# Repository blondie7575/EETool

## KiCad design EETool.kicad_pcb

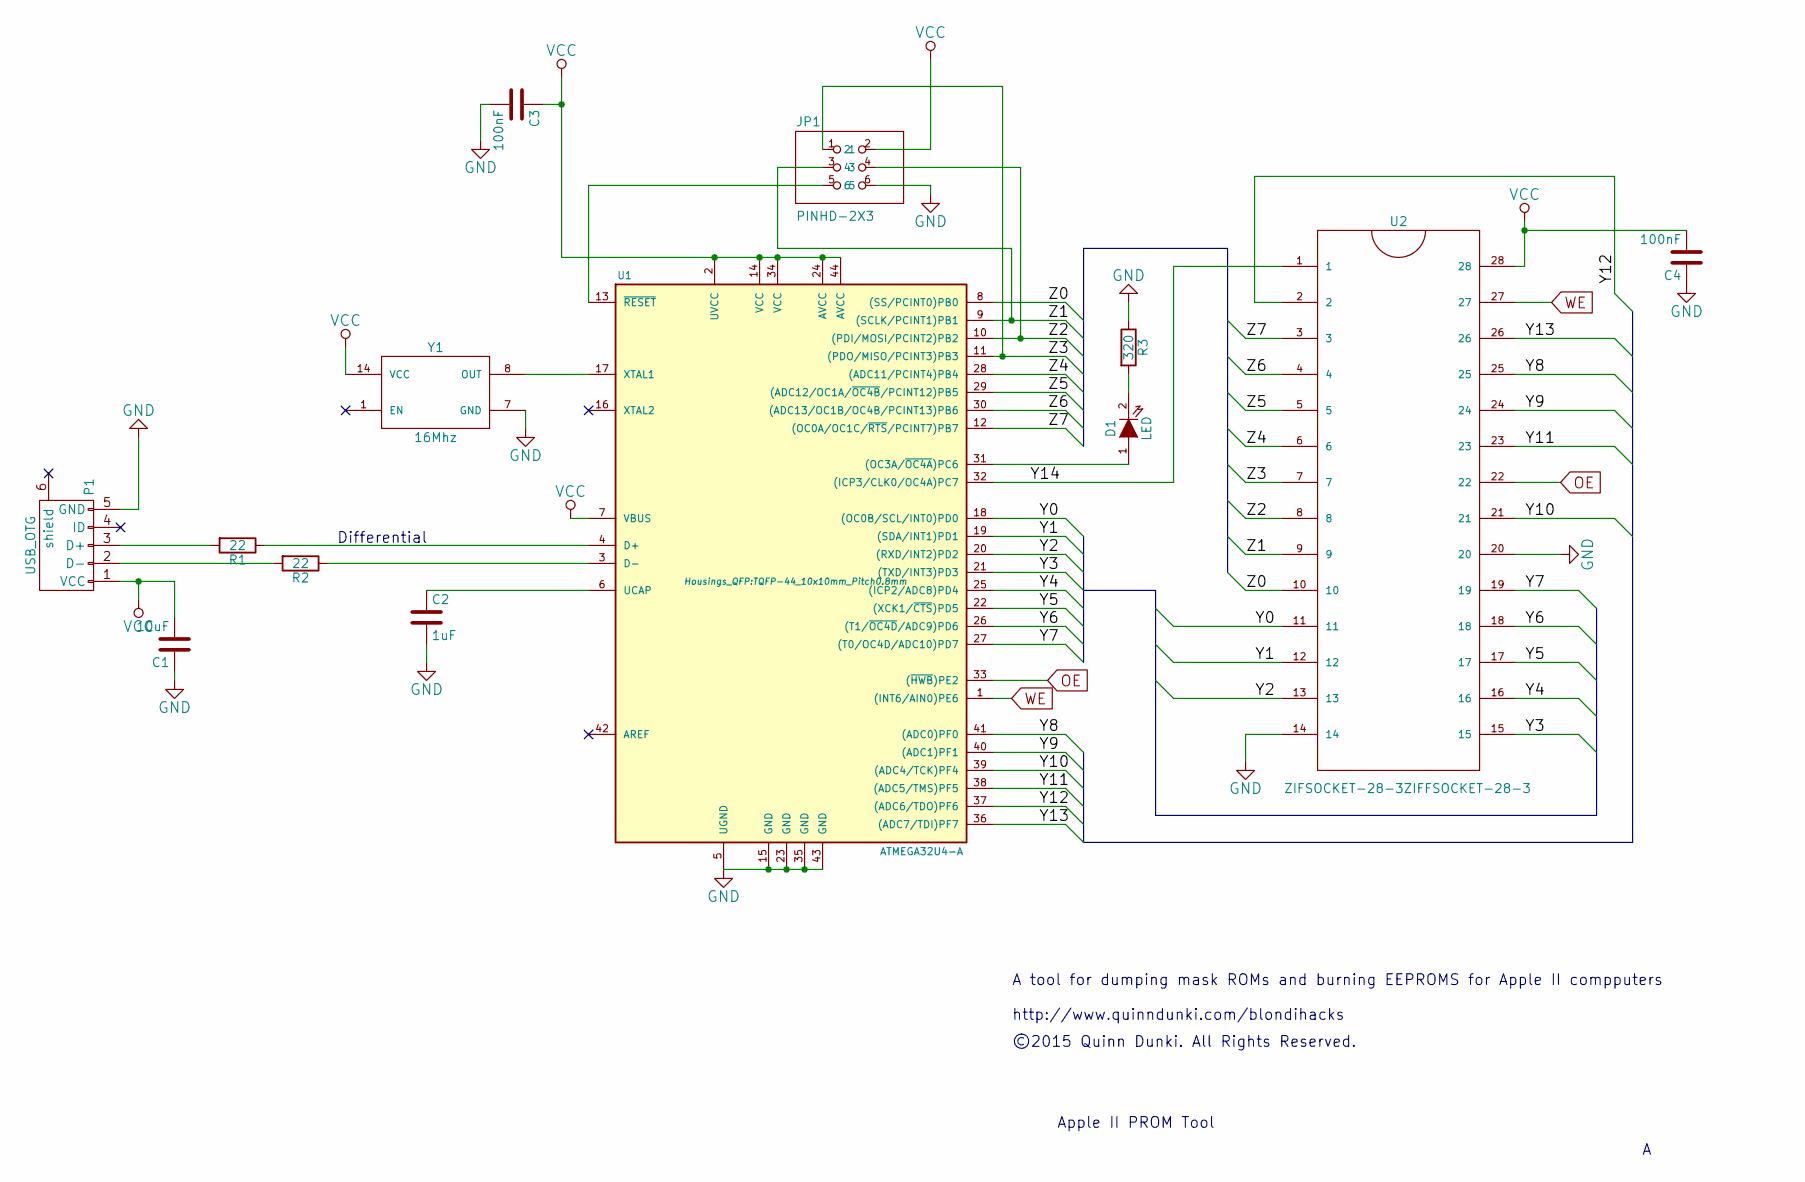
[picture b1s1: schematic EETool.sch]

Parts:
C1: 10uF; C_Rect_L18_W5_P15
C2: 1uF; C_Rect_L18_W5_P15
C3, C4: 100nF; C_Disc_D3_P2.5
D1: LED; LED-5MM
JP1: PINHD-2X3; Pin_Header_Straight_2x03
P1: USB_OTG; USB_B
R1, R2: 22; Resistor_Horizontal_RM10mm
R3: 320; Resistor_Horizontal_RM10mm
U1: ATMEGA32U4-A; TQFP-44_10x10mm_Pitch0.8mm
U2: ZIFSOCKET-28-3ZIFFSOCKET-28-3; DIP-28__600_ELL
Y1: 16Mhz; OSCILLATOR_KXO-200

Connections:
/Y0: U1.18 ((OC0B/SCL/INT0)PD0), U2.11
/Y1: U1.19 ((SDA/INT1)PD1), U2.12
/Y2: U1.20 ((RXD/INT2)PD2), U2.13
/Y3: U1.21 ((TXD/INT3)PD3), U2.15
/Y4: U1.25 ((ICP2/ADC8)PD4), U2.16
/Y5: U1.22 ((XCK1/~CTS~)PD5), U2.17
/Y6: U1.26 ((T1/~OC4D~/ADC9)PD6), U2.18
/Y7: U1.27 ((T0/OC4D/ADC10)PD7), U2.19
/Y8: U1.41 ((ADC0)PF0), U2.25
/Y9: U1.40 ((ADC1)PF1), U2.24
/Y10: U1.39 ((ADC4/TCK)PF4), U2.21
/Y11: U1.38 ((ADC5/TMS)PF5), U2.23
/Y12: U1.37 ((ADC6/TDO)PF6), U2.2
/Y13: U1.36 ((ADC7/TDI)PF7), U2.26
/Y14: U1.32 ((ICP3/CLK0/OC4A)PC7), U2.1
/Z0: U1.8 ((SS/PCINT0)PB0), U2.10
/Z1: JP1.3, U1.9 ((SCLK/PCINT1)PB1), U2.9
/Z2: JP1.4, U1.10 ((PDI/MOSI/PCINT2)PB2), U2.8
/Z3: JP1.1, U1.11 ((PDO/MISO/PCINT3)PB3), U2.7
/Z4: U1.28 ((ADC11/PCINT4)PB4), U2.6
/Z5: U1.29 ((ADC12/OC1A/~OC4B~/PCINT12)PB5), U2.5
/Z6: U1.30 ((ADC13/OC1B/OC4B/PCINT13)PB6), U2.4
/Z7: U1.12 ((OC0A/OC1C/~RTS~/PCINT7)PB7), U2.3
GND: C1.1, C2.2, C3.2, C4.1, JP1.6, P1.5 (GND), R3.1, U1.5 (UGND), U1.15 (GND), U1.23 (GND), U1.35 (GND), U1.43 (GND), U2.14, U2.20, Y1.7 (GND)
unnamed: C2.1, U1.6 (UCAP)
unnamed: D1.1 (A), U1.31 ((OC3A/~OC4A~)PC6)
unnamed: D1.2 (K), R3.2
unnamed: JP1.5, U1.13 (~RESET~)
unnamed: P1.2 (D-), R2.2
unnamed: P1.3 (D+), R1.2
unnamed: R1.1, U1.4 (D+)
unnamed: R2.1, U1.3 (D-)
unnamed: U1.17 (XTAL1), Y1.8 (OUT)
OE: U1.33 ((~HWB~)PE2), U2.22
VCC: C1.2, C3.1, C4.2, JP1.2, P1.1 (VCC), U1.2 (UVCC), U1.7 (VBUS), U1.14 (VCC), U1.24 (AVCC), U1.34 (VCC), U1.44 (AVCC), U2.28, Y1.14 (VCC)
WE: U1.1 ((INT6/AIN0)PE6), U2.27

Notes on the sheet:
Apple II PROM Tool
©2015 Quinn Dunki. All Rights Reserved.
A tool for dumping mask ROMs and burning EEPROMS for Apple II compputers http://www.quinndunki.com/blondihacks
Differential

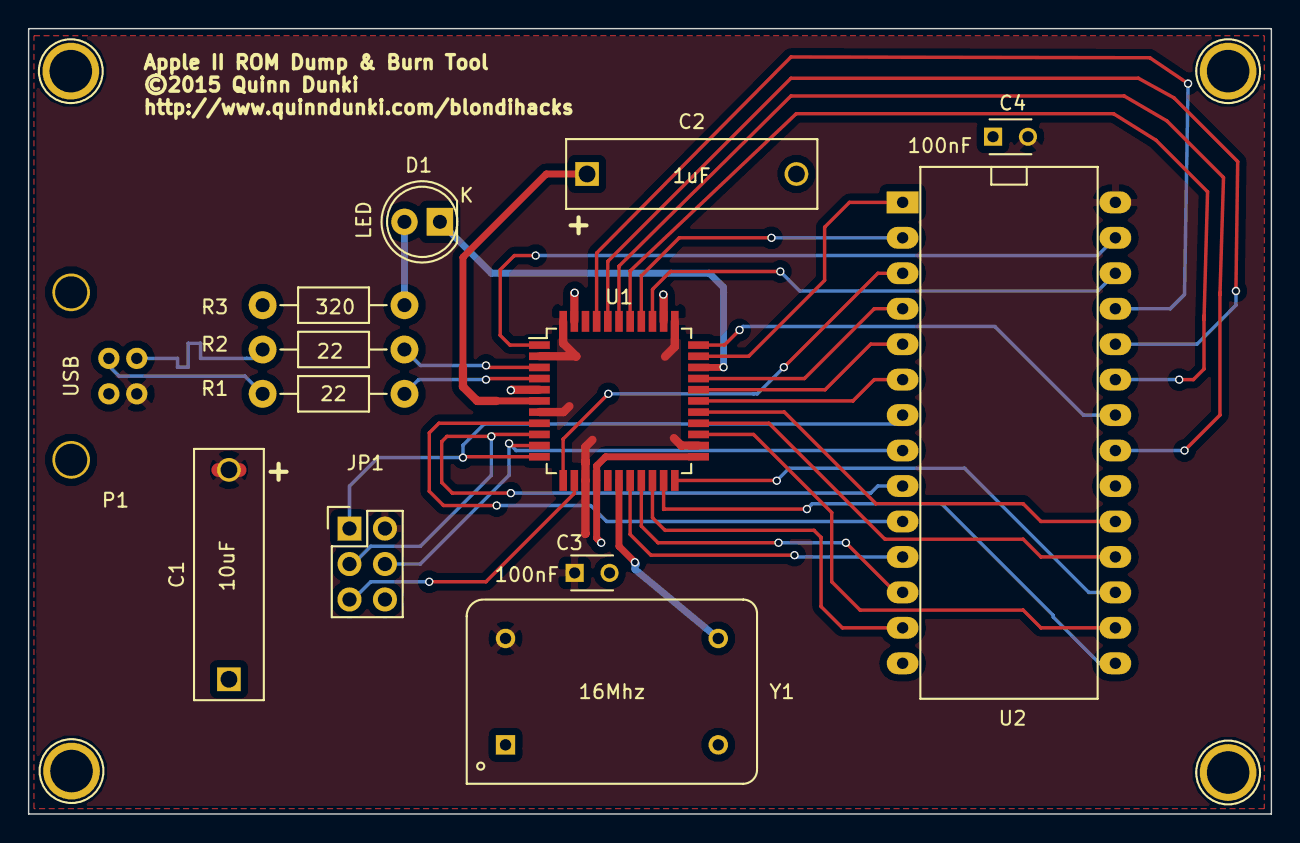
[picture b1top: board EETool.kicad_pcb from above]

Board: 2 copper layers, 89.0 x 56.3 mm, 13 parts (0 on the bottom side), 36 nets.

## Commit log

2015-08-25 Initial commit
    First proof of concept, dumps a 256kbit EEPROM
2015-09-05 Added CRC32 checksumming to dumping blocks
2015-09-06 Added support for reading mask ROMs
2015-09-06 Missed a file
2015-09-07 Test
2015-09-20 First pass on writing to EEPROMs
2015-09-20 Diff sample
2015-09-20 Cleanup
2015-10-11 Increased reliability
